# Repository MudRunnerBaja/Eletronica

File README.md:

# Eletronica
Repositório a ser usado apenas pelos membros de eletrônica da equipe baja do Cefet-RJ <br />
Por favor, ao fazer uma alteração no código, indicar o que foi alterado e colocar no READ.ME <br />

## Microcontroladores

- __Pic__:É um microcontrolador de arquitetura Harvard fabricado pela Microchip technology, ele tem a capacidade de processar dados de 8 bits, 16 bits e na versão mais atual, ele é capaz de processar dados de 32 bits. Ele possui uma alta velocidade de processamento devido a sua arquitetura Harvard, além disso, as famílias do MCU Pic  tem núcleos de processamento de 12bits, 14bits e 16bits, e trabalham em velocidade 0kHZ 48MHZ e velocidades de 16MIPS em alguns modelos.<br />   

- __Arduino__:Arduino é uma plataforma de prototipagem eletrônica de hardware livre e de placa única, projetada com um microcontrolador Atmel AVR com suporte de entrada/saída embutido, uma linguagem de programação padrão, a qual tem origem em Wiring, e é essencialmente C/C++.  Normalmente é utilizado em projetos mais simples e que não necessitam de conhecimento muito avançado sobre o firmware do microcontrolador (projetos caseiros).<br /> 

- __Esp32__:É um microcontrolador, que emprega um microprocessador de arquitetura Tensilica Xtensa LX6 de 32 bits com variações dual e single core e uma memória SRAM de 512Kb. Possui um clock máximo de 240 MHz. Ele também conta com wifi e bluetooth integrado.<br /> 

- __STM Arm__:STM32 é uma família de microcontroladores de 32 bits produzidos pela STMicroelectronics. Os chips STM32 são agrupados em séries relacionadas que são baseados em torno do mesmo núcleo do processador ARM de 32 bits, como o Cortex-M7, Cortex-M4F, Cortex-M3, Cortex-M0 +, ou Cortex-M0.<br /> 

- __RP2040__: O RP2040 é um microcontrolador de baixo custo e boa performance, criado pela Raspberry Pi. Trata-se de um processador Dual-Core ARM Cortex M0+, rodando em até 133MHz. Possui 264kB de memória SRAM e 2MB de memória Flash integrada na placa e pode ser programado em MicroPhython ou C/C++. O RP2040 possui 26 GPIOs multifunção, com 2x SPI, 2x I2C, 2x UART, 3x ADC de 12-bits e 16 canais PWM. Ela inclui um sensor de temperatura e bibliotecas para tratar ponto flutuante.<br />

### Microcontrolador escolhido pela equipe

O microcontrolador selecionado pela equipe é o RP2040, vendo sua alta performance, baixo custo e a possibilidade de ser programado pela IDE do arduino. A possibilidade de ser programado pela IDE do Arduino cria uma facilidade pela alta quantidade de bibliotecas, documentações e a familiaridade com a linguaguem de programação. Para usar esse microcontrolador, usamos a placa micro-controlada Raspberry Pi Pico.<br />

__Raspberry Pi Pico__

## Projetos
No momento foram implementadas as seguintes funcionalidades no carro:<br />

<ul>
  <li>Medição da temperatura da CVT</li>
  <li>GPS para localização e mapeamento do carro</li>
  <li>Medidor de combustível</li>
  <li>Leitura do RPM e da Velocidade</li>
  <li>Telemetria do carro</li>
  <li>Armazenamento de dados</li>
  <li>Chamada para o box</li>
</ul><br />

### Medição da temperatura da CVT
Atualmente, muitas equipes sofrem com superaquecimento gerado não só pelo atrito dos componentes presentes na CVT, como também pela falta de ventilação do local. Para resolver essa situação, a equipe decidiu desenvolver um sistema capaz de coletar a temperatura relativa à caixa interna da proteção da CVT, e enviar esses dados pela telemetria para o box. Dessa forma, podemos evitar o rompimento da correia ao detectar um sinal de aquecimento dentro do local. <br />

Após uma análise dos módulos a serem utilizados, o escolhido foi o módulo max6675 junto ao termopar tipo K, pois: <br />

<ul>
  <li>Atende a faixa de temperatura esperada (300 ºC)</li>
  <li>Possui o cabo revestido para não afetar no dado </li>
  <li>Possui uma boa precisão </li>
  <li>Facilidade de implementação no código </li>
  <li>Comunicação rápida (SPI) </li>
  <li>Ótimo custo benefício </li>
  <li>Possui na biblioteca do PROTEUS </li>
</ul><br />

<br />
*Fig 3 - Termopar max6675*<br />

```c
 /*
Código do pic 18f4550 para simulação da temperatura da CVT

Habilitar as seguintes bibliotecas:
- Lcd  e Lcd_Constants
- SPI
- Conversions e C_String e C_Type
- Uart
- C_Stdlib

Clock padrão: 20MHz
*/

#include <built_in.h>
#define tempmax 120

sbit LCD_RS at RB5_bit;
sbit LCD_EN at RB4_bit;
sbit LCD_D4 at RB3_bit;
sbit LCD_D5 at RB2_bit;
sbit LCD_D6 at RB1_bit;
sbit LCD_D7 at RB0_bit;

sbit LCD_RS_Direction at TRISB5_bit;
sbit LCD_EN_Direction at TRISB4_bit;
sbit LCD_D4_Direction at TRISB3_bit;
sbit LCD_D5_Direction at TRISB2_bit;
sbit LCD_D6_Direction at TRISB1_bit;
sbit LCD_D7_Direction at TRISB0_bit;

sbit MAX6675_CS at RC0_Bit;
sbit MAX6675_CS_Direction at TRISC0_Bit;

union{
  char state:1;
  char deviceID:1;
  char open:1;
  char temperature:12;
  char sign:1;
  unsigned output;
}Max6675Data;

void MAX6675_Init(){
  MAX6675_CS_Direction = 0;
  MAX6675_CS = 1;
}

unsigned Max6675_Read(){
unsigned tmp;
  MAX6675_CS = 0;
  Hi(tmp) = SPI1_Read(0);
  Lo(tmp) = SPI1_Read(0);
  MAX6675_CS = 1;
  return(tmp);
}

void main(){
char texto[8];
int temperatura;
   PCFG3_bit = 1; PCFG2_bit = 1; PCFG1_bit = 1; PCFG0_bit = 1;
   UART1_Init(9600);
   SPI1_Init();
   MAX6675_Init();
   Lcd_Init();
   Lcd_Cmd( _LCD_CURSOR_OFF );
   Lcd_Cmd( _LCD_CLEAR );
   Lcd_Out( 1, 6, "Temperatura CVT" );
   TRISD = 0;

   while(1)
   {
      *(unsigned*)&Max6675Data = MAX6675_Read();

      WordToStr( Max6675Data.temperature >> 1, texto );
      Lcd_Out( 2, 1, "Temp: " );
      Lcd_Out_CP( texto+2 );
      Lcd_Chr_CP( 223 );
      Lcd_Chr_CP( 'C' );
      UART1_Write_Text("temperatura:");
      UART1_Write_Text(texto);
      UART1_Write(13);

      temperatura = atoi(texto);

      if (temperatura >= tempmax){
      LATD.F0 = 1;
      }
      else{
      LATD.F0 = 0;
      }
      Delay_ms( 1000 );
   }
}
```

### GPS para localização e mapeamento do carro
O mapeamento de percurso é uma informação de suma importância para nossa equipe, visto que, com ela, é possível analisarmos possíveis falhas de direção, analisar as maiores dificuldades de nossos pilotos, saber se e onde o carro parou, e entre outros dados. O módulo GPS serve para transmitir em tempo real a localização do baja, a partir de dados como a longitude e a latitude. Esses dados podem posteriormente serem processados para mapear os locais visitados pelo carro, bem como sua atual posição. <br />

O módulo escolhido pela equipe foi o  GPS GY-NEO6MV2, por ser mais barato e de fácil utilização: <br />

<br />
*Fig 4 - GPS GY-NEO6MV2*<br />

```c
/*
Código do pic 18f4550 para simulação do GPS

Habilitar as seguintes bibliotecas:
- UART
- C_String

Clock padrão: 20MHz
*/

char txt[768];   // variavel txt para guardar todos os caracteres enviados pelo GPS
char *string;    // ponteiro para guardar a informação de interesse
int i,count,value;

void GPS(){
      int j;
      string = strstr(txt,"$GPGGA");    //String GPGGA contem as informações de latitude e longitude

      // Se a variavel string não for vazia, enviamos a latitude e longitude pela telemetria
      if(string != 0) {
          UART_Write_Text("latitude:");
          for(j = 18; j<27; j++)
              UART_Write(string[j]);
          UART_Write(13);
          UART_Write_Text("longitude:");
          for(j = 30; j<40; j++)
              UART_Write(string[j]);
          UART_Write(13);
      }
}

void interrupt(){
     if(TMR1IF_bit){
              count++;
              TMR1H= 0x0B;
              TMR1L= 0xDC;
              TMR1IF_bit = 0;
     }

     if(RCIF_bit){
              txt[i++] = UART1_Read();
              if(i==768) i=0;
              RCIF_bit = 0;
     }
}

void main() {
           PCFG3_bit = 1; PCFG2_bit = 1; PCFG1_bit = 1; PCFG0_bit = 1; // setando PORTA como digital ( evitar bugs )
           UART1_Init(9600);

           /*Configuração do timer 1 para obter o estouro desejado em ms
             Valores obtidos utilizando o clock padrão de 20MHz e preescaler de 8

              TMR1H = 0x0B;  TMR1L = 0xDC; ----> estouro de 100ms
              TMR1H = 0x85;  TMR1L = 0xEE; ----> estouro de 50ms
              TMR1H = 0xE7;  TMR1L = 0x96; ----> estouro de 10ms
              TMR1H = 0xF3;  TMR1L = 0xCB; ----> estouro de 5ms
              TMR1H = 0xFD;  TMR1L = 0x8F; ----> estouro de 1ms

           */
           TMR1IE_bit = 1;
           T1CON = 0b10110001;
           TMR1H = 0x0B;  TMR1L = 0xDC;

           TRISC.F0 = 0; // porta rc0 definida como saída

           // habilitando as interrupções globais, por periféricos e por UART
           GIE_bit = 1;
           PEIE_bit = 1;
           RCIE_bit = 1;

           while(1){

                    // count é incrementado a cada 100ms pelo timer 1, logo esse if será executado a cada 1segundo
                     if (count == 10){
                          count = 0;
                          value = ~value;
                          LATC.F0 = value;
                          GPS();
                     }

           }
}
```
### Medidor de combustível
O sistema de controle de nível de combustível é um dos circuitos mais importantes no carro, visto que com a noção do volume de gasolina presente no tanque, é possível prevenir a pane seca, que elimina a equipe da prova. Portanto, visando obter um maior tempo de carro na pista sem precisar reabastecer, é imprescindível que tenhamos um bom funcionamento nesse sistema.<br /> 

O módulo escolhido pela equipe foi o  LJC18A3,pois possui uma boa sensibilidade e é ajustável, permitindo uma melhor calibração. Já possuímos esses sensores na oficina e tivemos bons resultados com ele.<br />

<br />
*Fig 5 - Sensor capacitivo LJC18A3*<br />
### Leitura do RPM e da Velocidade

#### Velocidade
A velocidade do carro é um dado muito importante de se adquirir, visto que dá dados ao piloto para testar as melhores condições para fazer uma curva ou passar um obstáculo e é utilizada em diversos testes para a equipe. Com isso em mente, foi implementado um sensor de efeito hall, o qual detectava a pessagem de imãs no disco de freio. Posteriormente, vendo a imprecisão na aquisição da velocidade, causada pela folga axial no eixo da roda, o sistema de aquisição de velocidade foi substituido pela aquisição via GPS, a qual tem uma precisão de 0.1m/s.<br />

#### RPM
O motor de um baja é seu coração, portanto, controlar seu ‘batimento’ (RPM) é de suma importância para o time como um todo. É um dado imprescindível para análise de comportamento do motor, setagem de motor para TF, esforço do motor, quando mostrado ao piloto e entre outras situações.<br />

O motor utilizado possui 4 tempos que são: a admissão, a compressão, a explosão e a exaustão. Ao efetuar um ciclo completo (admissão, compressão, explosão e exaustão), uma indução eletromagnética da corrente é gerada pela bobina da vela. Para conseguir um bom valor de RPM, o sinal do motor precisa ser tratado antes dele ser transmitido para a placa. Esse tratamento de sinal se faz por filtros elétricos; com esse procedimento se espera ter um sinal na forma de onda quadrática com amplitude máxima de 3.3V.<br />

<br />
*Fig 7 - Sinal da bobina primária do motor sem o filtro e com o filtro*<br /> 

<br />
*Fig 8 - Filtro atual implementado pela equipe*<br />

### Telemetria
Dado agora que já somos capazes de implementar na prática todos os projetos acima mencionados, damos início ao nosso projeto da Telemetria. Irá funcionar como um sistema supervisório, em que todos os dados coletados são enviados por meio de um transmissor para nosso box. Dessa forma, todos da equipe poderam observar e perceber o que está se passando no carro, ajudando nas tomadas de decisão durante a prova.<br />
De modo geral, serão 2 desafios a serem superados. O primeiro consiste em juntar todos os projetos em um só. Já o segundo se resume na criação de um sistema supervisório e interativo, o qual ficou decidido que será um site.<br />
Para transmitir nossos dados, a equipe optou por escolher os seguintes componentes:<br />

- __Módulo HC-12:__ Tal módulo foi selecionado pela sua facilidade de uso, possui um custo baixo e atender a meta de telemetria de 800m, se utilizada com uma antena adequada. A antena helicoidal (que vem junto ao módulo) tem uma limitação de até 300-500m dependendo do local. É importante estar atento a escolha do próprio módulo, devendo ele ser ORIGINAL. Existem versões genéricas que limitam o alcance.<br />  

- __Antena monopólo vertical:__ https://www.youtube.com/watch?v=nQ4qYwILRjA Nesse video, há uma validação pratica com 2 diferentes antenas usando o HC12. Explicando o porquê de utilizar a antena monopólio vertical. Como ela pode ser fabricada por nós mesmos, de forma simples e barata, ela foi selecionada.<br />

<br />
*Fig 10 - Módulo HC 12 e antena*<br />

### Chamada para o box
A comunicação entre o piloto e o box durante a competição é algo muito importante para a equipe. Dessa forma, decidimos implementar um sistema de chamada para o box que será adicionado ao projeto da telemetria que a equipe já tem. Esse sistema consiste em uma comunicação bilateral onde o piloto tem a capacidade de avisar a equipe que ele está indo para o box ou a equipe pode chamar o piloto para ir para o box para reabastecer ou devido a um problema detectado no carro. <br />
A implementação será feita por meio da adição de um diodo LED no painel do carro para avisar o piloto que ele precisa ir para o box (a equipe chamando o piloto) e uma chave Push Button (Botão) para o piloto avisar a equipe que está indo ou querendo ir para o box. <br />

<br />
*Fig 11 - LEDs e Push Button*br />

## Testes
Os seguintes testes estão em desenvolvimento para auxíliar a equipe quanto a otimização dos componentes do carro<:br />

<ul>
  <li>Teste de Strain Gauge</li>
  <li>Teste de retomada e aceleração</li>
  <li>Teste de CVT Tunning</li>
  <li>Teste da variação do coeficiente de atrito da pastilha e do disco</li>
  <li>Teste de vibração</li>
</ul><br />

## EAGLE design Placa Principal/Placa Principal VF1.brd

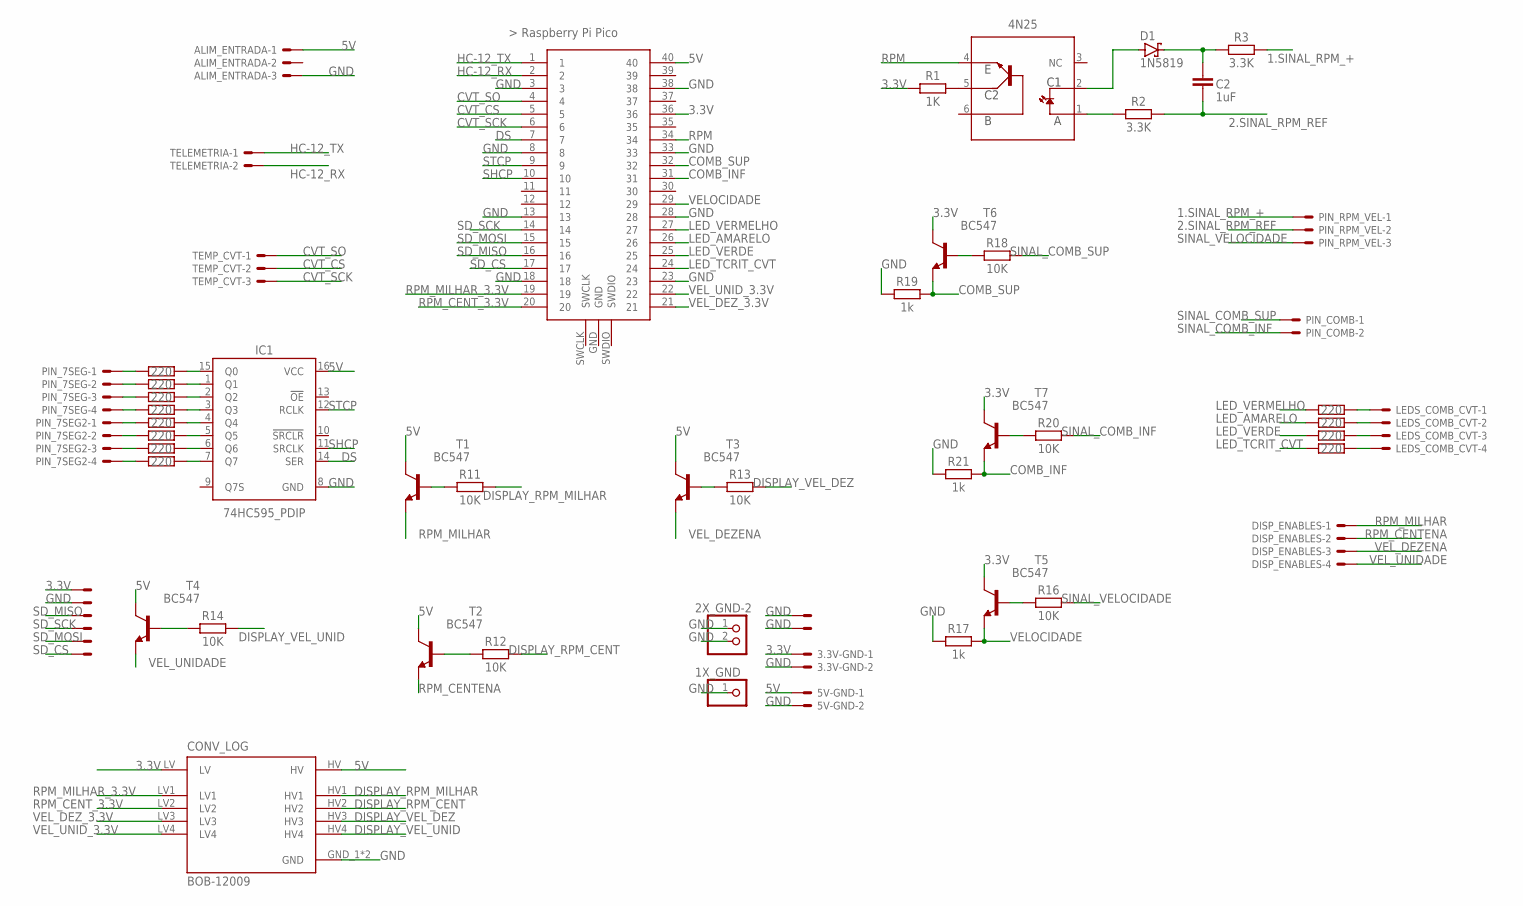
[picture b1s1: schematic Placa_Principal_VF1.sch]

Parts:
1X_GND: PINHD-1X1; 1X01
2X_GND, 3.3V, 3.3V-GND, 5V-GND: JST-XH-02-PIN-ROUND-PAD; JST-XH-02-PACKAGE-ROUND-PAD
2X_GND-2: PINHD-1X2; 1X02
4N25: 4N25; DIP762W60P254L712H480Q6B
ALIM_ENTRADA: JST-XH-03-PIN-ROUND-PAD; JST-XH-03-PACKAGE-ROUND-PAD
C2: 1uF; CAPRD550W60D1025H1250B
CONV_LOG: BOB-12009; CONV_BOB-12009
D1: 1N5819; DO41-7.6
DISP_ENABLES: JST-XH-04-PIN-ROUND-PAD; JST-XH-04-PACKAGE-ROUND-PAD
IC1: 74HC595_PDIP; DIP762W53P254L1969H508Q16B
LEDS_COMB_CVT: JST-XH-04-PIN-ROUND-PAD; JST-XH-04-PACKAGE-ROUND-PAD
MOD_SD: JST-XH-04-PIN-ROUND-PAD; JST-XH-04-PACKAGE-ROUND-PAD
PIN_7SEG, PIN_7SEG2: JST-XH-04-PIN-ROUND-PAD; JST-XH-04-PACKAGE-ROUND-PAD
PIN_COMB: JST-XH-02-PIN-ROUND-PAD; JST-XH-02-PACKAGE-ROUND-PAD
PIN_RPM_VEL: JST-XH-03-PIN-ROUND-PAD; JST-XH-03-PACKAGE-ROUND-PAD
R1: 1K; RESAD724W46L381D178B
R2, R3: 3.3K; RESAD724W46L381D178B
R4, R5, R6, R7, R8, R9, R10, R15, R22, R23, R24, R25: 220; RESAD724W46L381D178B
R11, R12, R13, R14, R16, R18, R20: 10K; RESAD724W46L381D178B
R17, R19, R21: 1k; RESAD724W46L381D178B
T1, T2, T3, T4, T5, T6, T7: BC547; TO92
TELEMETRIA: JST-XH-02-PIN-ROUND-PAD; JST-XH-02-PACKAGE-ROUND-PAD
TEMP_CVT: JST-XH-03-PIN-ROUND-PAD; JST-XH-03-PACKAGE-ROUND-PAD
U$2: RASPBERRY-PI-PICO_TH; FT_RASPBERRY-PI-PICO_TH

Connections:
1.SINAL_RPM_+: PIN_RPM_VEL.1, R3.2
2.SINAL_RPM_REF: C2.2, PIN_RPM_VEL.2, R2.2
3.3V: 3.3V.1, 3.3V-GND.1, CONV_LOG.LV, R1.1, T5.3 (C), T6.3 (C), T7.3 (C), U$2.36
5V: 5V-GND.1, ALIM_ENTRADA.1, CONV_LOG.HV, IC1.16 (VCC), T1.3 (C), T2.3 (C), T3.3 (C), T4.3 (C), U$2.40
COMB_INF: R21.2, T7.1 (E), U$2.31
COMB_SUP: R19.2, T6.1 (E), U$2.32
CVT_CS: TEMP_CVT.2, U$2.5
CVT_SCK: TEMP_CVT.3, U$2.6
CVT_SO: TEMP_CVT.1, U$2.4
DISPLAY_RPM_CENT: CONV_LOG.HV2, R12.2
DISPLAY_RPM_MILHAR: CONV_LOG.HV1, R11.2
DISPLAY_VEL_DEZ: CONV_LOG.HV3, R13.2
DISPLAY_VEL_UNID: CONV_LOG.HV4, R14.2
DS: IC1.14 (SER), U$2.7
GND: 1X_GND.1, 2X_GND.1, 2X_GND.2, 2X_GND-2.1, 2X_GND-2.2, 3.3V.2, 3.3V-GND.2, 5V-GND.2, ALIM_ENTRADA.3, CONV_LOG.GND_1 (GND), CONV_LOG.GND_2 (GND), IC1.8 (GND), R17.1, R19.1, R21.1, U$2.3, U$2.8, U$2.13, U$2.18, U$2.23, U$2.28, U$2.33, U$2.38
HC-12_RX: TELEMETRIA.2, U$2.2
HC-12_TX: TELEMETRIA.1, U$2.1
LED_AMARELO: R22.1, U$2.26
LED_TCRIT_CVT: R24.1, U$2.24
LED_VERDE: R23.1, U$2.25
LED_VERMELHO: R15.1, U$2.27
unnamed: 4N25.2 (C1), D1.A
unnamed: 4N25.1 (A), R2.1
unnamed: R16.1, T5.2 (B)
unnamed: C2.1, D1.C, R3.1
unnamed: R11.1, T1.2 (B)
unnamed: 4N25.5 (C2), R1.2
unnamed: IC1.15 (Q0), R4.2
unnamed: IC1.1 (Q1), R5.2
unnamed: IC1.2 (Q2), R6.2
unnamed: LEDS_COMB_CVT.1, R15.2
unnamed: R12.1, T2.2 (B)
unnamed: IC1.3 (Q3), R7.2
unnamed: IC1.4 (Q4), R8.2
unnamed: R13.1, T3.2 (B)
unnamed: IC1.5 (Q5), R9.2
unnamed: R18.1, T6.2 (B)
unnamed: LEDS_COMB_CVT.2, R22.2
unnamed: R14.1, T4.2 (B)
unnamed: IC1.6 (Q6), R10.2
unnamed: LEDS_COMB_CVT.3, R23.2
unnamed: R20.1, T7.2 (B)
unnamed: LEDS_COMB_CVT.4, R24.2
unnamed: IC1.7 (Q7), R25.2
unnamed: PIN_7SEG.1, R4.1
unnamed: PIN_7SEG.2, R5.1
unnamed: PIN_7SEG.3, R6.1
unnamed: PIN_7SEG.4, R7.1
unnamed: PIN_7SEG2.1, R8.1
unnamed: PIN_7SEG2.2, R9.1
unnamed: PIN_7SEG2.3, R10.1
unnamed: PIN_7SEG2.4, R25.1
RPM: 4N25.4 (E), U$2.34
RPM_CENTENA: DISP_ENABLES.2, T2.1 (E)
RPM_CENT_3.3V: CONV_LOG.LV2, U$2.20
RPM_MILHAR: DISP_ENABLES.1, T1.1 (E)
RPM_MILHAR_3.3V: CONV_LOG.LV1, U$2.19
SD_CS: MOD_SD.4, U$2.17
SD_MISO: MOD_SD.1, U$2.16
SD_MOSI: MOD_SD.3, U$2.15
SD_SCK: MOD_SD.2, U$2.14
SHCP: IC1.11 (SRCLK), U$2.10
SINAL_COMB_INF: PIN_COMB.2, R20.2
SINAL_COMB_SUP: PIN_COMB.1, R18.2
SINAL_VELOCIDADE: PIN_RPM_VEL.3, R16.2
STCP: IC1.12 (RCLK), U$2.9
VELOCIDADE: R17.2, T5.1 (E), U$2.29
VEL_DEZENA: DISP_ENABLES.3, T3.1 (E)
VEL_DEZ_3.3V: CONV_LOG.LV3, U$2.21
VEL_UNIDADE: DISP_ENABLES.4, T4.1 (E)
VEL_UNID_3.3V: CONV_LOG.LV4, U$2.22

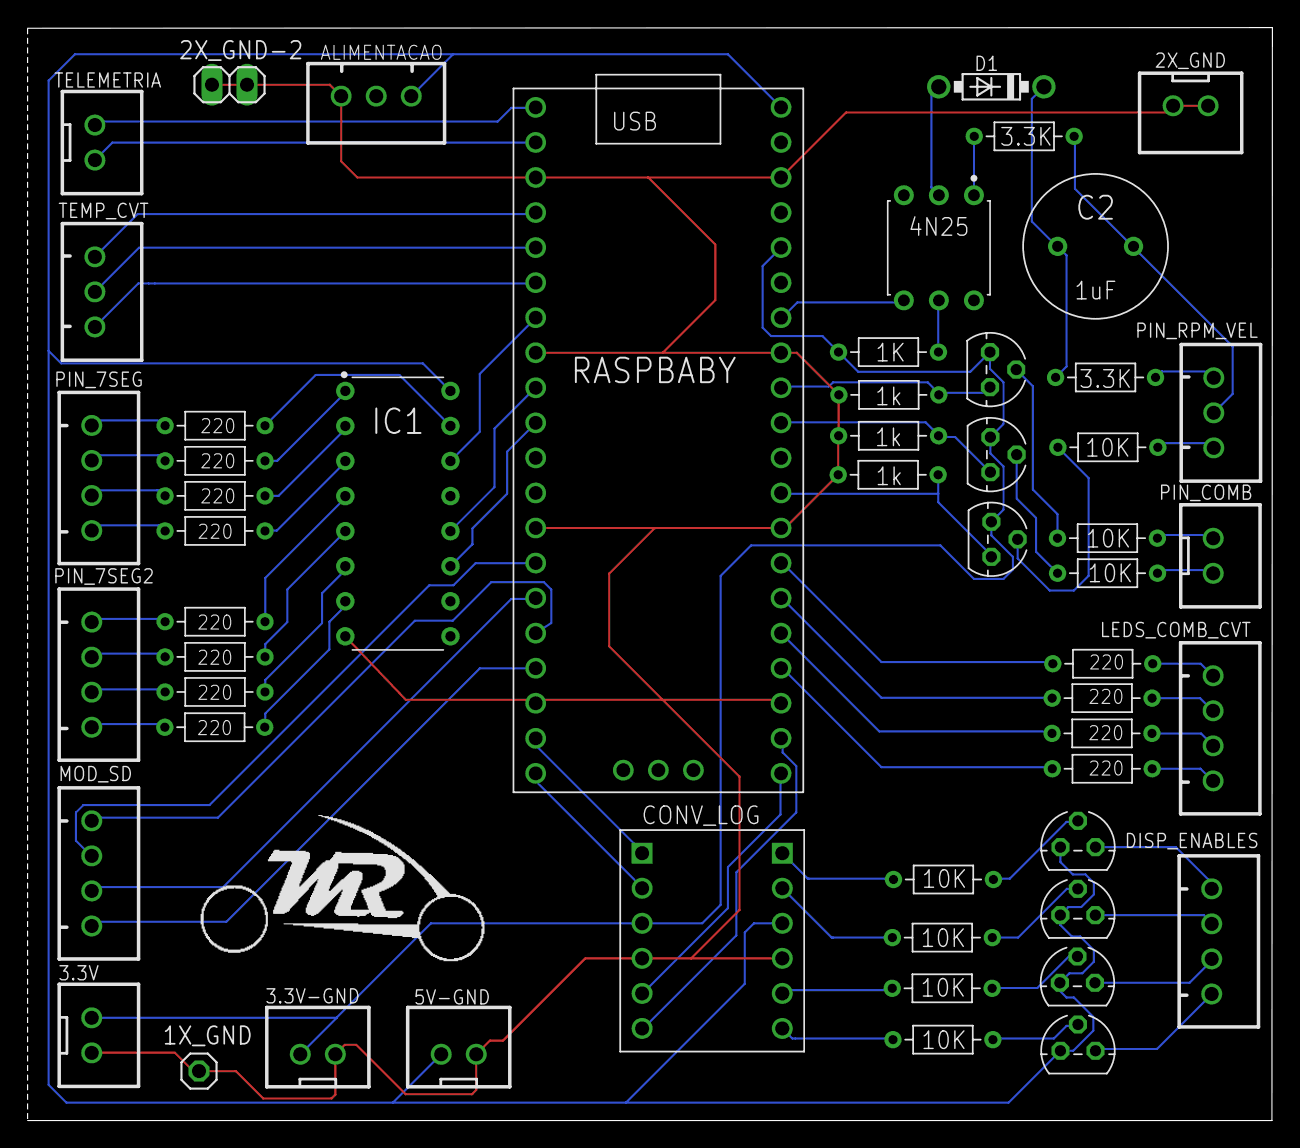
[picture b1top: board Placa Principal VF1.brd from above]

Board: 2 copper layers, 90.2 x 79.2 mm, 54 parts (0 on the bottom side), 71 nets.

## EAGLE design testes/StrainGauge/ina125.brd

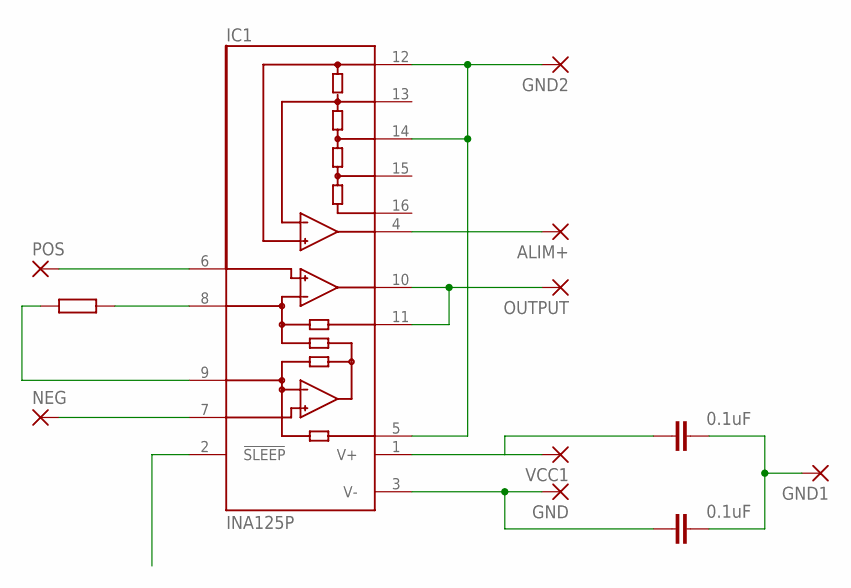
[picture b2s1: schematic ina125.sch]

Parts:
ALIM+: 1,6/0,8
C1, C2: 0.1uF; C2.5-3
GND, GND1, GND2: 1,6/0,8
IC1: INA125P; DIL16
NEG: 1,6/0,8
OUTPUT: 1,6/0,8
POS: 1,6/0,8
VCC1: 1,6/0,8

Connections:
unnamed: C2.1, GND.1, IC1.3 (V-)
unnamed: C1.2, C2.2, GND1.1
unnamed: C1.1, IC1.1 (V+), VCC1.1
unnamed: IC1.10 (OUT), IC1.11 (SENSE), OUTPUT.1
unnamed: IC1.6 (+IN), POS.1
unnamed: IC1.7 (-IN), NEG.1
unnamed: ALIM+.1, IC1.4 (REFOUT)
unnamed: GND2.1, IC1.5 (REF), IC1.12 (REFCOM), IC1.14 (REF2.5)

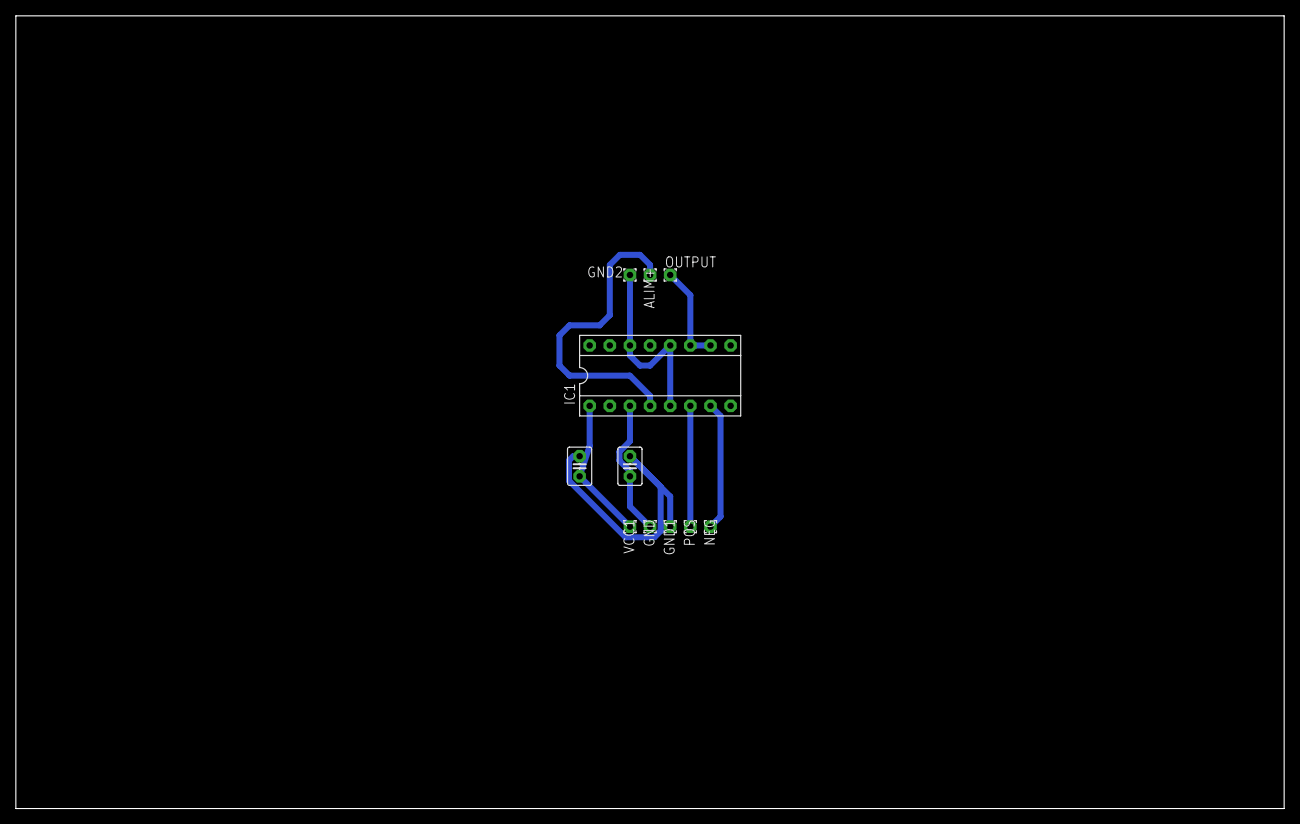
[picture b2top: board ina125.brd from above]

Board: 2 copper layers, 160.0 x 100.0 mm, 11 parts (0 on the bottom side), 8 nets.

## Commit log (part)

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2020-05-20 simulacao
2020-05-21 organizando o git
2020-05-21 Projeto telemetria antigo
2020-05-31 correcao bugs
2020-07-23 Create main.c
    Código principal atualizado com strain gauge *nao testado*
2020-12-07 Troquei o nome do .jpg
2020-12-26 adicionando imagem da simulação do box
2021-04-03 Create placasEagle
2021-07-12 Adicionado o arquivo de 30m
2021-08-17 Bump ini from 1.3.5 to 1.3.8 in /telemetria/telemetria_v2
    Bumps [ini](https://github.com/isaacs/ini) from 1.3.5 to 1.3.8.
    - [Release notes](https://github.com/isaacs/ini/releases)
    - [Commits](https://github.com/isaacs/ini/compare/v1.3.5...v1.3.8)
    ---
    updated-dependencies:
    - dependency-name: ini
2021-08-23 Iniciando telemetria e re-organização das pastas
2022-02-17 Adicionado sistema com o tema da equipe
2022-02-20 Adicionado rota usuário
2022-02-21 Adicionado GPS
2022-04-07 Atualização de pinos + alterações servidor
2022-04-12 Correção rpm
2022-04-15 Esquema da placa do display
2022-07-27 Atualização da Placa Principal
    Corrigido um pequeno erro nas trilhas e adicionada uma pequena modificação no design
2022-08-17 Adicionado a função de velocidade
2022-08-22 Novas funções e corrigido erros de gravação
2022-08-23 Falhas corrigidas
2022-08-31 Portas corrigidas para o novo modelo de placa
2022-09-20 IC Charlieplexado
    Tentativa de manter o brilho do display reduzindo o consumo de corrente. Se bem sucedido:
    - Mantém o projeto da placa
    - Mantém o custo dos componentes da placa
    - Evita o uso de gambiarras e soluções externas (como placas com transistores)
2022-09-21 Bump minimist from 1.2.5 to 1.2.6 in /telemetria/Antigo
    Bumps [minimist](https://github.com/substack/minimist) from 1.2.5 to 1.2.6.
    - [Release notes](https://github.com/substack/minimist/releases)
    - [Commits](https://github.com/substack/minimist/compare/1.2.5...1.2.6)
    ---
    updated-dependencies:
    - dependency-name: minimist
2022-09-21 Bump moment-timezone in /telemetria/Sistema_tema_equipe/Sistema
    Bumps [moment-timezone](https://github.com/moment/moment-timezone) from 0.5.34 to 0.5.37.
    - [Release notes](https://github.com/moment/moment-timezone/releases)
    - [Changelog](https://github.com/moment/moment-timezone/blob/develop/changelog.md)
    - [Commits](https://github.com/moment/moment-timezone/compare/0.5.34...0.5.37)
    ---
    updated-dependencies:
2022-09-21 Bump sqlite3 in /telemetria/Sistema_tema_equipe/Sistema
    Bumps [sqlite3](https://github.com/TryGhost/node-sqlite3) from 5.0.2 to 5.0.3.
    - [Release notes](https://github.com/TryGhost/node-sqlite3/releases)
    - [Changelog](https://github.com/TryGhost/node-sqlite3/blob/master/CHANGELOG.md)
    - [Commits](https://github.com/TryGhost/node-sqlite3/compare/v5.0.2...v5.0.3)
    ---
    updated-dependencies:
2022-09-30 Implementado múltipla criação de arquivos no SD
2022-10-20 Update SDCard
2022-10-25 Revert "Update sdcard.c"
    This reverts commit ab002c03ba32cec3cbdfa6e41cc4ba4b598456bb.
2022-11-04 Esquemática do novo filtro de RPM
2022-11-15 Testes pré-regional
2022-12-08 Bump qs and express in /telemetria/Antigo
    Bumps [qs](https://github.com/ljharb/qs) to 6.11.0 and updates ancestor dependency [express](https://github.com/expressjs/express). These dependencies need to be updated together.
    Updates `qs` from 6.7.0 to 6.11.0
    - [Release notes](https://github.com/ljharb/qs/releases)
    - [Changelog](https://github.com/ljharb/qs/blob/main/CHANGELOG.md)
    - [Commits](https://github.com/ljharb/qs/compare/v6.7.0...v6.11.0)
    Updates `express` from 4.17.1 to 4.18.2
2022-12-20 implementando novo gps
2022-12-22 Preparação do setup
2022-12-22 Setup timer e getcomb
2022-12-22 fault handling sdcard
2022-12-22 debugging code
2022-12-25 Corrigido erro na atribuição de uma função
2023-01-19 Código-Teste para Otimização
    Limitando tempo de encoding do GPS para evitar prender o processador por longos períodos de tempo;
    Checagem se os dados salvos foram recentemente atualizados ou não;
    É necessário reestruturar o sistema de biblioteca
2023-01-29 Implementado a interface de configuração
    Ainda a fazer:
    Salvar horário usando o gps
    Não gravar dados enquanto o gps não estiver sincronizado com os satelites
2023-02-02 Teste Completo
2023-02-06 fixes
2023-02-07 Comentarios adicionados
2023-02-10 Pre-Teste
2023-02-12 Contador de rpm da movida
2023-02-13 Adaptaçao cartao SD CVT Tuning
2023-02-16 Fix i2c
2023-02-17 Renaming and changing to header files
2023-02-21 Improved interface
2023-02-23 Bump sequelize in /telemetria/Sistema_tema_equipe/Sistema
    Bumps [sequelize](https://github.com/sequelize/sequelize) from 6.16.1 to 6.28.2.
    - [Release notes](https://github.com/sequelize/sequelize/releases)
    - [Commits](https://github.com/sequelize/sequelize/compare/v6.16.1...v6.28.2)
    ---
    updated-dependencies:
    - dependency-name: sequelize
2023-02-24 Added new functions
2023-02-25 Bump sequelize in /telemetria/Sistema_tema_equipe/Sistema
    Bumps [sequelize](https://github.com/sequelize/sequelize) from 6.16.1 to 6.29.0.
    - [Release notes](https://github.com/sequelize/sequelize/releases)
    - [Commits](https://github.com/sequelize/sequelize/compare/v6.16.1...v6.29.0)
    ---
    updated-dependencies:
    - dependency-name: sequelize
2023-03-07 Bump minimist in /telemetria/Sistema_tema_equipe/Sistema
    Bumps [minimist](https://github.com/minimistjs/minimist) from 1.2.5 to 1.2.8.
    - [Release notes](https://github.com/minimistjs/minimist/releases)
    - [Changelog](https://github.com/minimistjs/minimist/blob/main/CHANGELOG.md)
    - [Commits](https://github.com/minimistjs/minimist/compare/v1.2.5...v1.2.8)
    ---
    updated-dependencies:
2023-04-05 Add files via upload
    Teste simples! Só para ver quando o receptor parou de receber!
2023-05-31 Atualizando Testes de Telemetria
    Agora envia uma data que é quebrada em dias/mes/ano de um sender para um receiver.
    a distância do sinal chegou a 130m sem obstruções tranquilamente.
2023-07-06 Teste de Distancia Standalone adicionado
2023-07-06 Teste comunicacao serial1 e serial2 pico consigo mesmo (Sem sucesso)
2023-08-01 Atualizado pra main. Precisa de revisao
2023-08-16 Implementação no codigo da placa principal
2023-12-11 readme e configurações de projeto
2023-12-16 Teste telemetria pico-ft232 adaptado
2024-01-10 back end funcionando usando serial por emulado
    informações no arquivo teste emulacao serial, mongo db.informacoes só recebe o id do data sheet e não os valores verificar parser
2024-01-11 inicio projeto frontend
2024-01-24 json stringfy arduino data back -> front
2024-02-06 Update TestePressaoFreio.ino
    Adicionado comentarios
2024-02-20 Adicao de libs ao novo sketch placa central
2024-02-21 Bump ip from 2.0.0 to 2.0.1 in /telemetria/frontend
    Bumps [ip](https://github.com/indutny/node-ip) from 2.0.0 to 2.0.1.
    - [Commits](https://github.com/indutny/node-ip/compare/v2.0.0...v2.0.1)
    ---
    updated-dependencies:
    - dependency-name: ip
    dependency-type: indirect
2024-02-29 Libs sensor temperatura mlx90614
2024-03-06 Codigos de teste CAN-BUS funcional
2024-03-18 cod placa central WIP
2024-03-23 Estruturacao das bibliotecas compilavel para arduino-pico
2024-03-29 Bump express from 4.18.2 to 4.19.2 in /telemetria/frontend
    Bumps [express](https://github.com/expressjs/express) from 4.18.2 to 4.19.2.
    - [Release notes](https://github.com/expressjs/express/releases)
    - [Changelog](https://github.com/expressjs/express/blob/master/History.md)
    - [Commits](https://github.com/expressjs/express/compare/4.18.2...4.19.2)
    ---
    updated-dependencies:
2024-05-09 implementacao combustivel
2024-05-14 Teste do limite de rpm
2024-05-20 Correções e ajuste biblioteca GPS
2024-05-24 WIP refatoracao telemetria - separacao da logica e configuracao de infra
2024-06-04 Transformando classes em singletons
2024-06-11 Implementado menus e layout atualizado
2024-06-14 static struct com dados
2024-07-22 correcoes inicializacao
2024-08-03 struct global de dados para simplificar troca de info
2025-02-20 fix antigos
2025-02-27 substituicao prints debug
2025-04-29 Bump http-proxy-middleware and @angular-devkit/build-angular
    Bumps [http-proxy-middleware](https://github.com/chimurai/http-proxy-middleware) to 3.0.5 and updates ancestor dependency [@angular-devkit/build-angular](https://github.com/angular/angular-cli). Thes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
    Updates `http-proxy-middleware` from 2.0.6 to 3.0.5
    - [Release notes](https://github.com/chimurai/http-proxy-middleware/releases)
    - [Changelog](https://github.com/chimurai/http-proxy-middleware/blob/master/CHANGELOG.md)
    - [Commits](https://github.com/chimurai/http-proxy-middleware/compare/v2.0.6...v3.0.5)
    Updates `@angular-devkit/build-angular` from 17.1.1 to 19.2.9
2025-05-29 can bus compilando, velocidade e rpm funcionais
2025-06-04 Bump webpack-dev-server and @angular-devkit/build-angular
    Bumps [webpack-dev-server](https://github.com/webpack/webpack-dev-server) to 5.2.1 and updates ancestor dependency [@angular-devkit/build-angular](https://github.com/angular/angular-cli). These depen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
    Updates `webpack-dev-server` from 4.15.1 to 5.2.1
    - [Release notes](https://github.com/webpack/webpack-dev-server/releases)
    - [Changelog](https://github.com/webpack/webpack-dev-server/blob/master/CHANGELOG.md)
    - [Commits](https://github.com/webpack/webpack-dev-server/compare/v4.15.1...v5.2.1)
    Updates `@angular-devkit/build-angular` from 17.1.1 to 20.0.1
2025-06-09 Codigo modificado para o primeiro teste
2025-06-10 codificacao funcional, TODO: decodificacao e reorganizacao de pacotes
2025-08-19 codigo que ta no pc de eletronica
2025-09-09 é necessário fazer structs menores para passar os dados
2025-09-10 codigo enviando dados com sucesso pela telemetria. Ainda é necessário fazer um cleanup no código para a versão final
2025-09-19 mudei alguma coisas de dados
2025-09-25 verifiquei k
2025-10-28 Bump validator in /telemetria/old/Sistema_tema_equipe/Sistema
    Bumps [validator](https://github.com/validatorjs/validator.js) from 13.7.0 to 13.15.20.
    - [Release notes](https://github.com/validatorjs/validator.js/releases)
    - [Changelog](https://github.com/validatorjs/validator.js/blob/master/CHANGELOG.md)
    - [Commits](https://github.com/validatorjs/validator.js/compare/13.7.0...13.15.20)
    ---
    updated-dependencies:
2025-11-26 Bump node-forge from 1.3.1 to 1.3.2 in /telemetria/frontend
    Bumps [node-forge](https://github.com/digitalbazaar/forge) from 1.3.1 to 1.3.2.
    - [Changelog](https://github.com/digitalbazaar/forge/blob/main/CHANGELOG.md)
    - [Commits](https://github.com/digitalbazaar/forge/compare/v1.3.1...v1.3.2)
    ---
    updated-dependencies:
    - dependency-name: node-forge
2025-12-01 Bump express from 4.18.2 to 4.22.0 in /telemetria/backend
    Bumps [express](https://github.com/expressjs/express) from 4.18.2 to 4.22.0.
    - [Release notes](https://github.com/expressjs/express/releases)
    - [Changelog](https://github.com/expressjs/express/blob/4.22.0/History.md)
    - [Commits](https://github.com/expressjs/express/compare/4.18.2...4.22.0)
    ---
    updated-dependencies:
2025-12-31 Bump qs and express in /telemetria/old/Antigo
    Bumps [qs](https://github.com/ljharb/qs) to 6.14.1 and updates ancestor dependency [express](https://github.com/expressjs/express). These dependencies need to be updated together.
    Updates `qs` from 6.7.0 to 6.14.1
    - [Changelog](https://github.com/ljharb/qs/blob/main/CHANGELOG.md)
    - [Commits](https://github.com/ljharb/qs/compare/v6.7.0...v6.14.1)
    Updates `express` from 4.17.1 to 4.22.1
    - [Release notes](https://github.com/expressjs/express/releases)
2026-01-21 Bump lodash in /telemetria/old/Sistema_tema_equipe/Sistema
    Bumps [lodash](https://github.com/lodash/lodash) from 4.17.21 to 4.17.23.
    - [Release notes](https://github.com/lodash/lodash/releases)
    - [Commits](https://github.com/lodash/lodash/compare/4.17.21...4.17.23)
    ---
    updated-dependencies:
    - dependency-name: lodash
2026-02-05 Bump semver from 5.7.1 to 5.7.2 in /telemetria/old/Antigo
    Bumps [semver](https://github.com/npm/node-semver) from 5.7.1 to 5.7.2.
    - [Release notes](https://github.com/npm/node-semver/releases)
    - [Changelog](https://github.com/npm/node-semver/blob/v5.7.2/CHANGELOG.md)
    - [Commits](https://github.com/npm/node-semver/compare/v5.7.1...v5.7.2)
    ---
    updated-dependencies:
2026-02-26 sei lá
